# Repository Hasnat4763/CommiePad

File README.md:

# CommiePad
This is my macropad!
# Features:

6 neopixel LEDs!
6 Cherry MX keys
1 Rotary Encoder with switch
1 I2C display

# Schematic

# PCB

# CAD

I used Fusion 360 for it. It was my 1st time making something 3D so it took a lot of time Without calculating the load sheddings(Thanks BD Govt for so many load sheddings ;-) ).
It fits with 4 m3 screws and bolts

# Firmware:
I used KMK firmware but I havent finalized it yet!

# BOM:

1 SEEED XIAO RP2040

6 Cherry MX switch

1 EC11 Rotary encoder

6 SK6812 MINI-E LEDs

1 0.91 inch OLED display

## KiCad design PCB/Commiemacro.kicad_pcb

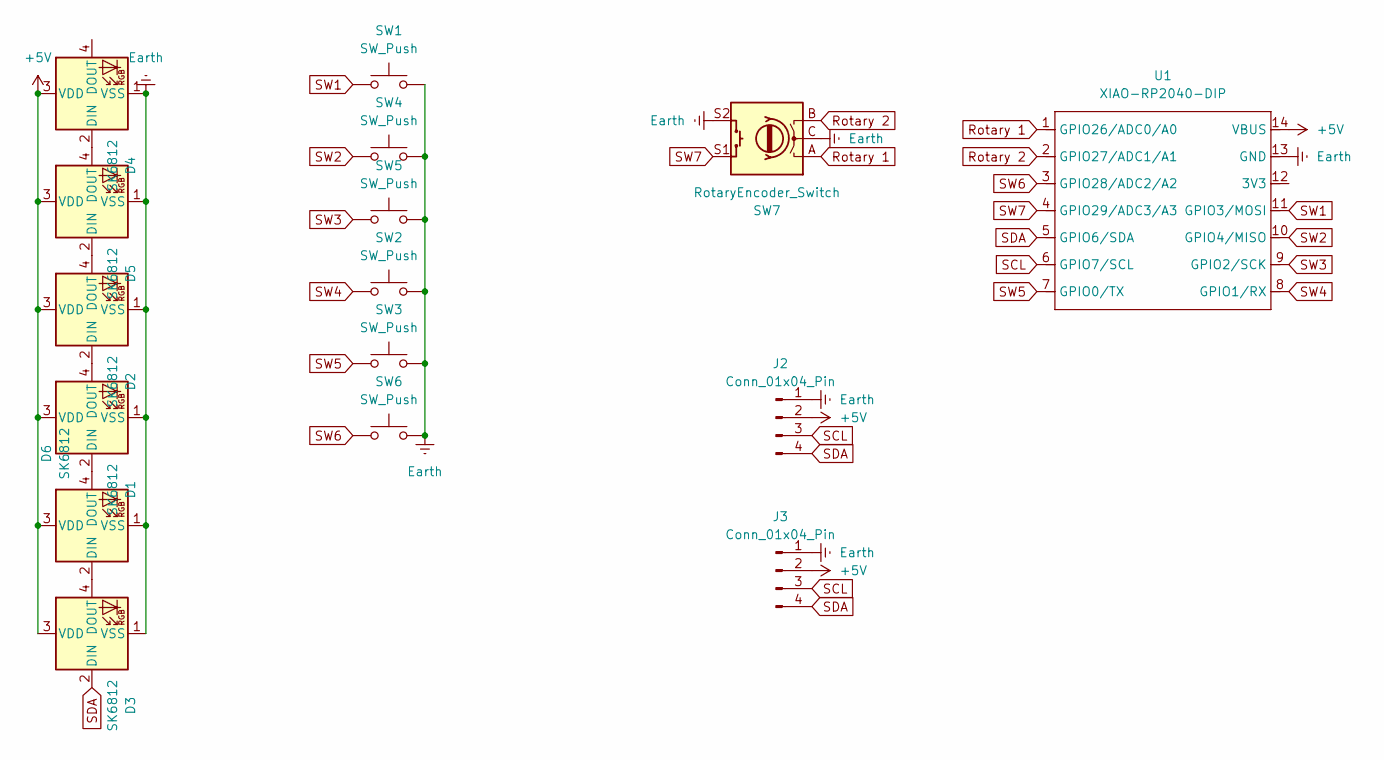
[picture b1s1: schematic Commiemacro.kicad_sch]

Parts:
D1, D2, D3, D4, D5, D6: SK6812; LED_SK6812_PLCC4_5.0x5.0mm_P3.2mm
J2, J3: Conn_01x04_Pin; NS-Tech_Grove_1x04_P2mm_Vertical
SW1, SW2, SW3, SW4, SW5, SW6: SW_Push; SW_Cherry_MX_1.00u_PCB
SW7: RotaryEncoder_Switch; RotaryEncoder_Alps_EC11E-Switch_Vertical_H20mm
U1: XIAO-RP2040-DIP

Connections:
+5V: D1.3 (VDD), D2.3 (VDD), D3.3 (VDD), D4.3 (VDD), D5.3 (VDD), D6.3 (VDD), J2.2, J3.2, U1.14 (VBUS)
Earth: D1.1 (VSS), D2.1 (VSS), D3.1 (VSS), D4.1 (VSS), D5.1 (VSS), D6.1 (VSS), J2.1, J3.1, SW1.2, SW2.2, SW3.2, SW4.2, SW5.2, SW6.2, SW7.C, SW7.S2, U1.13 (GND)
unnamed: D1.2 (DIN), D6.4 (DOUT)
unnamed: D1.4 (DOUT), D2.2 (DIN)
unnamed: D2.4 (DOUT), D5.2 (DIN)
unnamed: D3.4 (DOUT), D6.2 (DIN)
unnamed: D4.2 (DIN), D5.4 (DOUT)
Rotary 1: SW7.A, U1.1 (GPIO26/ADC0/A0)
Rotary 2: SW7.B, U1.2 (GPIO27/ADC1/A1)
SCL: J2.3, J3.3, U1.6 (GPIO7/SCL)
SDA: D3.2 (DIN), J2.4, J3.4, U1.5 (GPIO6/SDA)
SW1: SW1.1, U1.11 (GPIO3/MOSI)
SW2: SW4.1, U1.10 (GPIO4/MISO)
SW3: SW5.1, U1.9 (GPIO2/SCK)
SW4: SW2.1, U1.8 (GPIO1/RX)
SW5: SW3.1, U1.7 (GPIO0/TX)
SW6: SW6.1, U1.3 (GPIO28/ADC2/A2)
SW7: SW7.S1, U1.4 (GPIO29/ADC3/A3)

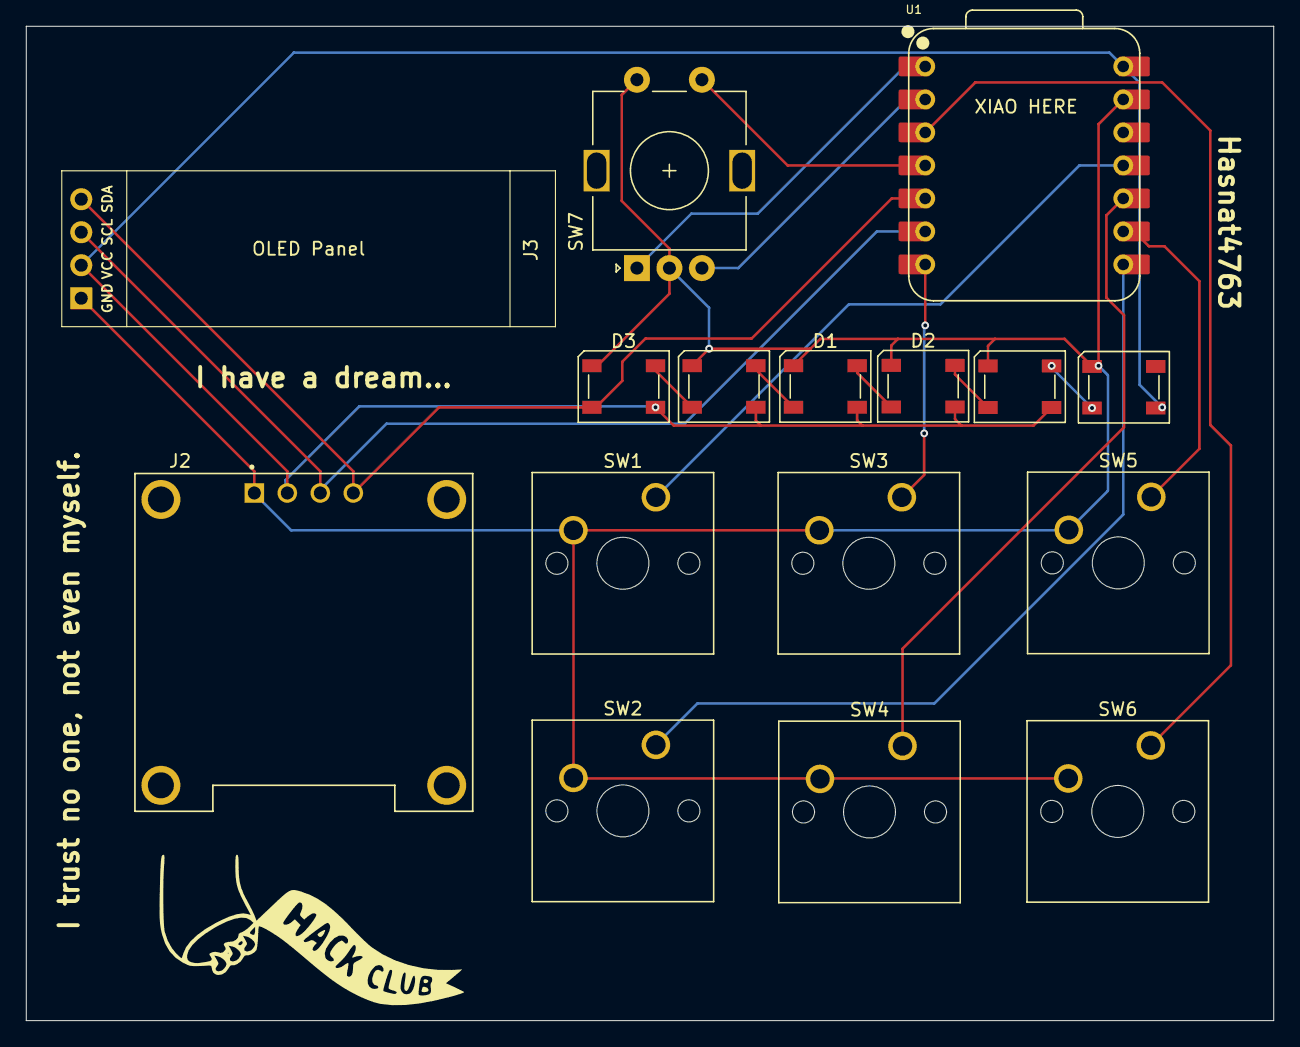
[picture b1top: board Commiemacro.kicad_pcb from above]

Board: 2 copper layers, 96.0 x 76.5 mm, 16 parts (0 on the bottom side), 18 nets.

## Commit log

2025-06-02 Adding all the files
